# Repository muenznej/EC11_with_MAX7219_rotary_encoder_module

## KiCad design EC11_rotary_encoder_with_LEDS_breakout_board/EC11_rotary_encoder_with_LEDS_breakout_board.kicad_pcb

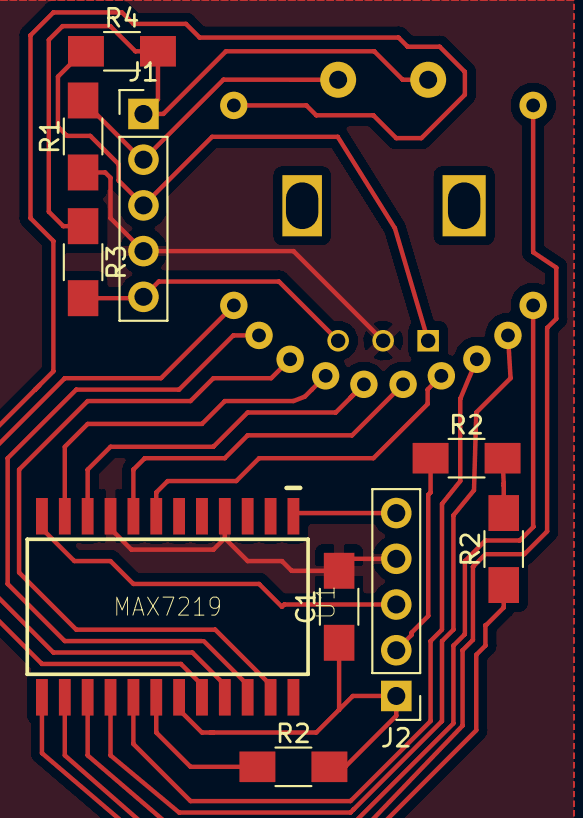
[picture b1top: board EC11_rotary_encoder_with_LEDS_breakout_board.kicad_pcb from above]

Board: 2 copper layers, 11 parts (1 on the bottom side), 21 nets.

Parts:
C1: 100n; R_1206_HandSoldering
ENC1: EC11_LED_Rotary; RotaryEncoder_Alps_EC11E-Switch_Vertical_H20mm_with_LED
J1, J2: Conn_01x05; Pin_Header_Straight_1x05_Pitch2.54mm
R1, R3, R4: 10k; R_1206_HandSoldering
R2, R2#2, R2#3: 28k; R_1206_HandSoldering
U1: MAX7219; SOIC24

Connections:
+5V: C1.1, ENC1.SW2, J1.1, J2.1, R2#3.2, R3.1, R4.2, U1.19
/BTN: ENC1.SW1, J1.2, R1.2
/CLK: J2.2, R2.1, R2.2, R2#2.1, R2#2.2, U1.13
/DIN: J2.5, U1.1
/EncoderA: ENC1.A, J1.3, R4.1
/EncoderB: ENC1.B, J1.5, R3.2
/LOAD: J2.3, U1.12
GND: C1.2, ENC1.C, J1.4, J2.4, R1.1, U1.4, U1.9
unnamed: ENC1.1, U1.14
unnamed: ENC1.2, U1.15
unnamed: ENC1.3, U1.16
unnamed: ENC1.4, U1.17
unnamed: ENC1.5, U1.7
unnamed: ENC1.6, U1.8
unnamed: ENC1.7, U1.10
unnamed: ENC1.8, U1.11
unnamed: ENC1.9, U1.23
unnamed: ENC1.10, U1.22
unnamed: ENC1.11, U1.21
unnamed: ENC1.12, U1.20
unnamed: R2#3.1, U1.18
